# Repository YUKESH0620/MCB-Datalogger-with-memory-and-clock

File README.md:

# MCU Datalogger with Memory and Real-Time Clock

A compact, low-power data-logging board designed in KiCad (v9.0.4). The board is built around an ATmega328P-AU microcontroller, a DS1337S real-time clock (RTC) with a 32.768 kHz crystal, and two 24LC1025 I²C EEPROM devices for extended timestamped data storage. The design is a 2-layer custom PCB sized 87.63mm × 39.116mm and is powered by a coin-cell battery (BT1) for RTC backup. Data can be accessed via I²C or UART; the MCU is programmable by ICSP or a UART bootloader.

---

## Overview

This project is a lightweight, modular data logger intended for timestamped sensor data collection. It provides:

- Reliable timekeeping (DS1337S with coin-cell backup)
- Extended non-volatile storage (two 24LC1025 EEPROMs)
- Standard interfaces for integration (I²C, UART, GPIO, ICSP)
- A compact 2-layer PCB designed in KiCad 9.0.4

---

## Features

- Microcontroller: ATmega328P-AU (16 MHz)
- Real-time clock: DS1337S with 32.768 kHz crystal
- Non-volatile memory: 2 × 24LC1025 EEPROM (I²C)
- Connectivity: I²C header, UART (RX/TX) header, GPIO header, 6-pin ICSP
- Indicators: 2 status LEDs
- Power: Coin-cell Battery (BT1) for RTC backup
- Board: 2-layer PCB; 87.63 mm × 39.116 mm; 4 mounting holes
- KiCad version: 9.0.0

---

## Hardware Architecture

High-level blocks:

- MCU (ATmega328P-AU): central controller for data acquisition, timestamping, and storage
- RTC (DS1337S): battery-backed real-time clock (I²C)
- EEPROMs (2 × 24LC1025): extended I²C non-volatile storage
- Headers: I²C, UART, GPIO, and ICSP for programming and peripherals
- Power: Coin-cell for RTC backup; decoupling and power filtering on-board

Notable electrical details:

- MCU clock: 16 MHz crystal (Y2) with C2 = 22 pF and C3 = 22 pF
- RTC: DS1337S with 32.768 kHz crystal; pull-ups R1 = 10 kΩ, R2 = 10 kΩ; decoupling C1 = 0.1 µF
- EEPROMs: Two 24LC1025 on I²C with pull-ups R3 = 4.7 kΩ and R4 = 4.7 kΩ
- Status LEDs: D1 (R5 = 330 Ω), D2 (R7 = 330 Ω)
- Power decoupling: C4 = 0.1 µF

---

## Schematic

- Schematic Page 1 — Main MCU, RTC, EEPROM

- Schematic Page 2 — Connectors

Refer to the KiCad schematic files in the repo for full net names, pin labels, and design notes.

---

## PCB Layout
### 2 layer

### 4 layer

### 3D View

#### PCB summary

| Property | Value |
|---|---:|
| Layers | 2 |
| Dimensions | 87.63 mm × 39.116 mm |
| Mounting holes | 4 |
| Silkscreen | Labeled pins (I²C, UART, GPIO, ICSP) |
| Unrouted nets | 0 |
| KiCad version | 9.0 |

---

## Connectors / Pinout

- I²C header (4-pin): SDA, SCL, VCC, GND
- UART header (3-pin): RX, TX, GND (VCC optional)
- GPIO header: multiple MCU GPIO pins broken out (see schematic)
- ICSP (6-pin): MISO, MOSI, SCK, RESET, VCC, GND

---

## Bill of Materials (BOM)

| Ref | Qty | Part | Notes |
|---|---:|---|---|
| U1 | 1 | ATmega328P-AU | 28-pin TQFP |
| U2 | 1 | DS1337S | RTC (I²C) |
| U3, U4 | 2 | 24LC1025 | I²C EEPROM |
| Y2 | 1 | Crystal | 16 MHz (MCU) |
| Y1 | 1 | Crystal | 32.768 kHz (RTC) |
| BT1 | 1 | Battery | CR2032 or equivalent (observe polarity) |
| C1, C4 | 2 | 0.1 µF | Ceramic decoupling caps |
| C2, C3 | 2 | 22 pF | Crystal load caps |
| R1, R2 | 2 | 10 kΩ | RTC pull-ups |
| R3, R4 | 2 | 4.7 kΩ | EEPROM pull-ups |
| R5, R7 | 2 | 330 Ω | LED current-limiting |
| D1, D2 | 2 | LED | SMD or THT per footprint |
| J1 (I²C) | 1 | Header | 4-pin |
| J2 (UART) | 1 | Header | 3-pin |
| J3 (GPIO) | 1 | Header | n-pin |
| J4 (ICSP) | 1 | 6-pin ICSP | 2×3 2.54 mm |
| Mounting holes | 4 | M3 | Mechanical mounting |

Full, exportable BOM (CSV) and placement files are provided in the repo (see /bom and /fab folders if present).

---

## How to Use

Assembly:

- Solder SMD components first (MCU, RTC, EEPROMs, resistors, capacitors), then through-hole parts (headers, coin cell holder).
- Observe polarity for LEDs and coin cell.
- Place crystals and load capacitors as shown in schematic.

Power:

- Supply VCC according to the chosen components (3.3 V or 5 V depending on populated parts). Confirm the RTC and EEPROM voltage ranges before applying power.
- Coin cell provides RTC backup via the VBAT connection on the DS1337S. Ensure correct polarity and secure holder.

Basic operation:

- The MCU collects sensor data (I²C/GPIO), requests current time from the DS1337S, and writes time-stamped entries to the EEPROM(s).
- Retrieve logs via UART (connect a USB‑to‑TTL adapter: RX→TX, TX→RX, GND→GND) at the baud rate set by the firmware.
- Optionally access EEPROMs directly over I²C from a host microcontroller or logic analyzer.

I²C notes:

- On-board pull-ups are provided (R1/R2 for RTC, R3/R4 for EEPROM). If your external bus already includes pull-ups, verify combined pull-up resistance is within recommended limits.
- Addressing: consult the 24LC1025 datasheet for device addressing and block management if both EEPROMs use similar address pins.

---

## Programming the MCU

ICSP (recommended for initial programming and bootloader burn):

- Connect a 6-pin ISP programmer (USBasp, AVRISP, etc.) to the ICSP header: MISO, MOSI, SCK, RESET, VCC, GND.
- Example avrdude command (USBasp):

  avrdude -c usbasp -p m328p -U flash:w:firmware.hex

UART (if a bootloader is installed):

- Use a USB‑to‑TTL adapter to the UART header. Typical Arduino/Optiboot settings for 16 MHz apply if using Arduino core.
- To burn a bootloader via Arduino IDE, connect an ISP programmer and select the appropriate board/frequency, then Tools → Burn Bootloader.

Firmware recommendations:

- Implement time queries to DS1337S via I²C and write structured records to EEPROM with checksums.
- Implement wear-leveling or a ring-buffer log scheme to maximize EEPROM lifespan.
- Provide a simple UART command set for log extraction and configuration.

---

<!--## Testing & Validation

- Verify MCU oscillator and boot behavior after programming.
- Confirm RTC register reads/writes and timekeeping across coin-cell swaps.
- Use an I²C scanner to validate device addresses for RTC and EEPROMs.
- Test UART responses and data export functionality. -->

## Future Improvements

- Add optional power domain/regulator for external supplies with coin-cell backup for RTC.
- Add battery charging and low-battery detection circuitry.
- Add footprints for common sensors (temperature, humidity, pressure) on-board.
- Implement hardware write-protect for EEPROMs and optional encryption of stored logs.
- Provide a 3D-printable enclosure and mounting guides.

---

## Contributing

Contributions are welcome. Please:

- Open an issue to discuss non-trivial changes before submitting a PR.
- Submit focused pull requests with updated KiCad files, Gerbers, and BOM when hardware changes are included.
- Keep commit messages clear and include rationale for electrical or layout changes.

---

## Safety

- Coin cells are a choking hazard and can be dangerous if swallowed—keep away from children.
- Handle ESD-sensitive parts with appropriate precautions.
- Verify coin-cell polarity before installing.

---

## License

This project is provided under the MIT License. See LICENSE for details.

---

## Contacts

For questions or collaboration, open an issue or contact the repository owner (YUKESH0620) via GitHub.

---

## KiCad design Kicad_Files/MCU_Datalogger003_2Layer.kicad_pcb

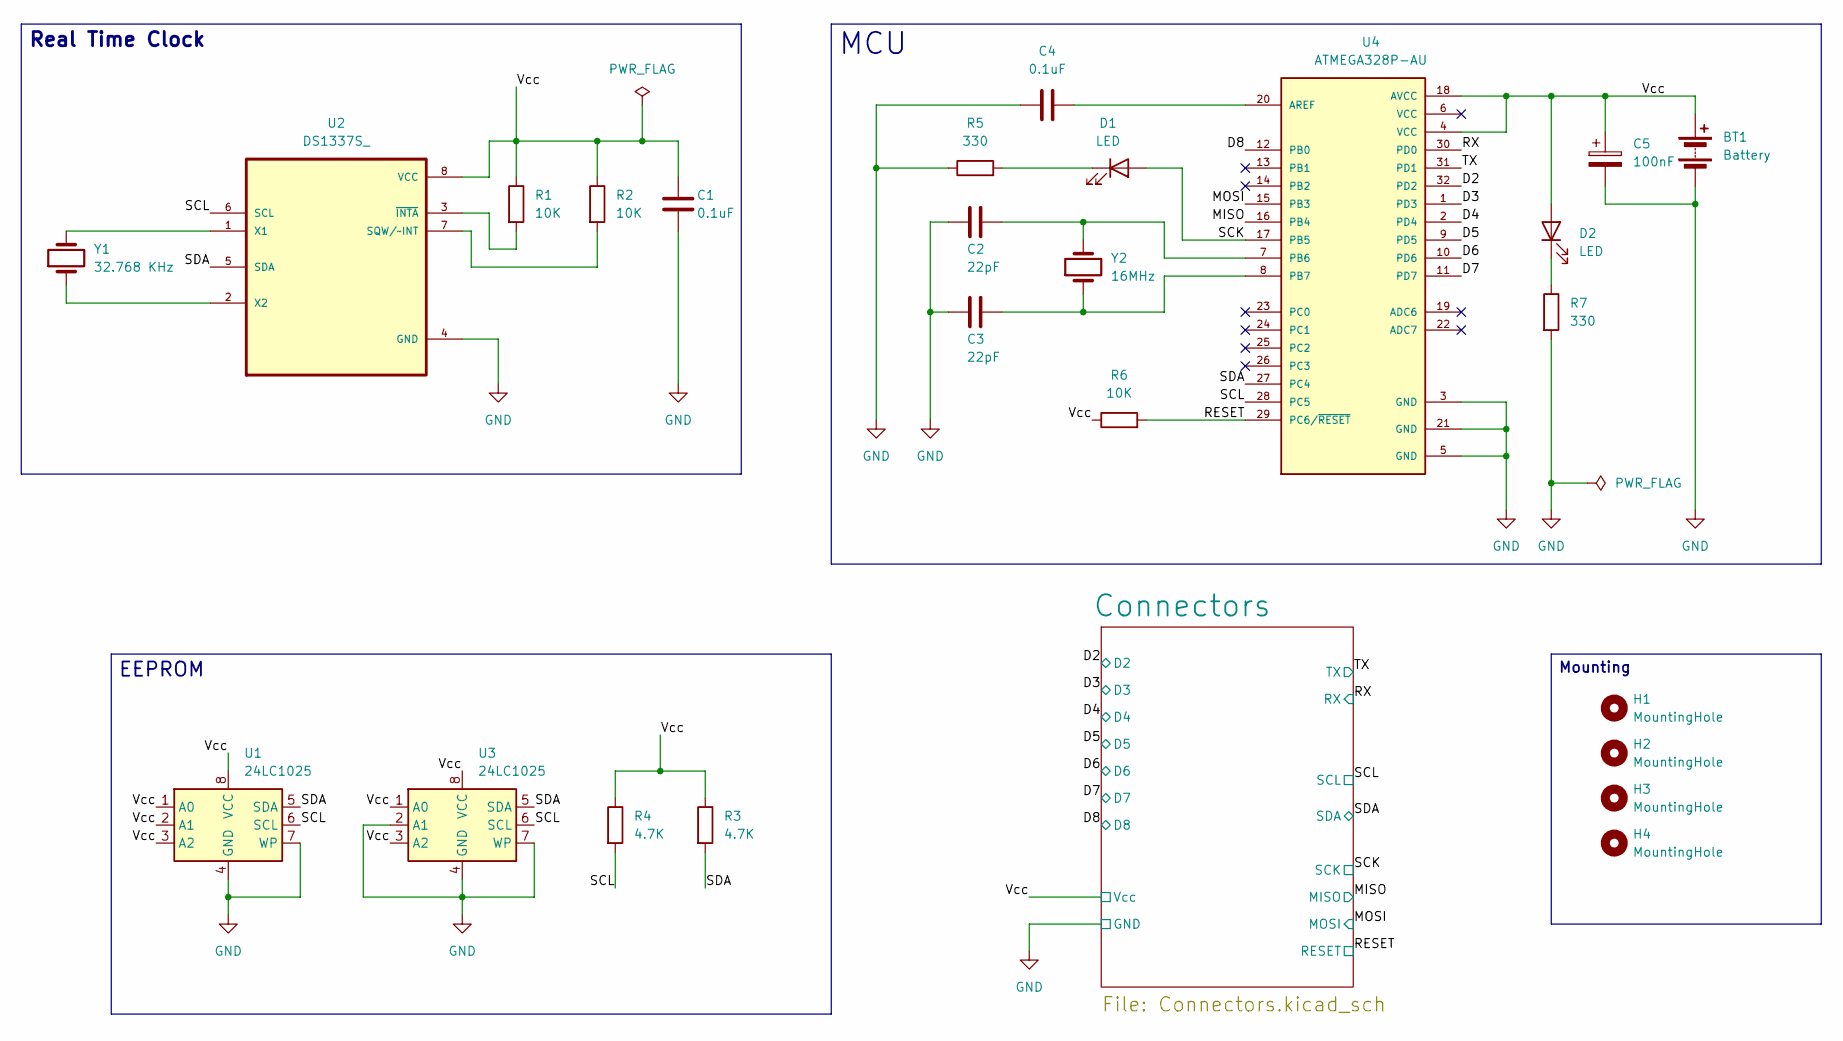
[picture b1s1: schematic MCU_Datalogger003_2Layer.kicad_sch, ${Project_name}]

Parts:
BT1: Battery; PinHeader_1x02_P2.54mm_Vertical
C1, C4: 0.1uF; C_0805_2012Metric
C2, C3: 22pF; C_0805_2012Metric
C5: 100nF; C_0805_2012Metric
D1, D2: LED; LED_0805_2012Metric
H1, H2, H3, H4: MountingHole; MountingHole_2.1mm
R1, R2, R6: 10K; R_0805_2012Metric
R3, R4: 4.7K; R_0805_2012Metric
R5, R7: 330; R_0805_2012Metric
U1, U3: 24LC1025; SOIC-8_5.3x5.3mm_P1.27mm
U2: DS1337S_; RT-CLOCK_SOIC127P600X175-8N
U4: ATMEGA328P-AU; ATMEGA328P-AUQFP80P900X900X120-32N; PARTREV 8271A
Y1: 32.768 KHz; Crystal_SMD_5032-2Pin_5.0x3.2mm_HandSoldering
Y2: 16MHz; Crystal_SMD_5032-2Pin_5.0x3.2mm_HandSoldering

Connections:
/D2: U4.32 (PD2); also elsewhere on the board
/D3: U4.1 (PD3); also elsewhere on the board
/D4: U4.2 (PD4); also elsewhere on the board
/D5: U4.9 (PD5); also elsewhere on the board
/D6: U4.10 (PD6); also elsewhere on the board
/D7: U4.11 (PD7); also elsewhere on the board
/D8: U4.12 (PB0); also elsewhere on the board
/MISO: U4.16 (PB4); also elsewhere on the board
/MOSI: U4.15 (PB3); also elsewhere on the board
/RESET: R6.2, U4.29 (PC6/~RESET); also elsewhere on the board
/RX: U4.30 (PD0); also elsewhere on the board
/SCK: D1.2 (A), U4.17 (PB5); also elsewhere on the board
/SCL: R4.2, U1.6 (SCL), U2.6 (SCL), U3.6 (SCL), U4.28 (PC5); also elsewhere on the board
/SDA: R3.2, U1.5 (SDA), U2.5 (SDA), U3.5 (SDA), U4.27 (PC4); also elsewhere on the board
/TX: U4.31 (PD1); also elsewhere on the board
/Vcc: BT1.1 (+), C1.1, C5.1, D2.2 (A), R1.1, R2.1, R3.1, R4.1, R6.1, U1.1 (A0), U1.2 (A1), U1.3 (A2), U1.8 (VCC), U2.8 (VCC), U3.1 (A0), U3.3 (A2), U3.8 (VCC), U4.4 (VCC), U4.18 (AVCC); also elsewhere on the board
GND: BT1.2 (-), C1.2, C2.2, C3.2, C4.1, C5.2, R5.1, R7.2, U1.4 (GND), U1.7 (WP), U2.4 (GND), U3.2 (A1), U3.4 (GND), U3.7 (WP), U4.3 (GND), U4.5 (GND), U4.21 (GND); also elsewhere on the board
unnamed: D1.1 (K), R5.2
unnamed: D2.1 (K), R7.1
unnamed: R2.2, U2.7 (SQW/~INT)
unnamed: U2.1 (X1), Y1.2
unnamed: U2.2 (X2), Y1.1
unnamed: R1.2, U2.3 (~INTA)
unnamed: C4.2, U4.20 (AREF)
unnamed: C2.1, U4.7 (PB6), Y2.2
unnamed: C3.1, U4.8 (PB7), Y2.1

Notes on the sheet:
EEPROM
Mounting
Real Time Clock
MCU

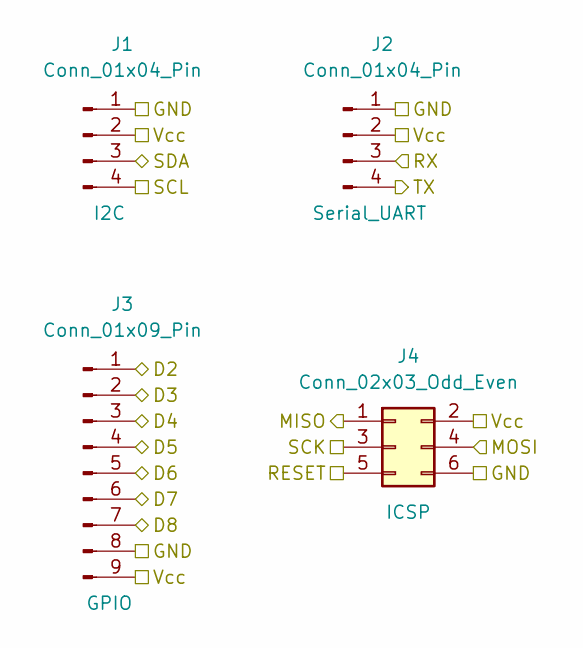
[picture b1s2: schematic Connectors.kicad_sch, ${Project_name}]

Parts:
J1, J2: Conn_01x04_Pin; PinHeader_1x04_P2.54mm_Vertical
J3: Conn_01x09_Pin; PinHeader_1x09_P2.54mm_Vertical
J4: Conn_02x03_Odd_Even; PinHeader_2x03_P2.54mm_Vertical

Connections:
/D2: J3.1; also elsewhere on the board
/D3: J3.2; also elsewhere on the board
/D4: J3.3; also elsewhere on the board
/D5: J3.4; also elsewhere on the board
/D6: J3.5; also elsewhere on the board
/D7: J3.6; also elsewhere on the board
/D8: J3.7; also elsewhere on the board
/MISO: J4.1; also elsewhere on the board
/MOSI: J4.4; also elsewhere on the board
/RESET: J4.5; also elsewhere on the board
/RX: J2.3; also elsewhere on the board
/SCK: J4.3; also elsewhere on the board
/SCL: J1.4; also elsewhere on the board
/SDA: J1.3; also elsewhere on the board
/TX: J2.4; also elsewhere on the board
/Vcc: J1.2, J2.2, J3.9, J4.2; also elsewhere on the board
GND: J1.1, J2.1, J3.8, J4.6; also elsewhere on the board

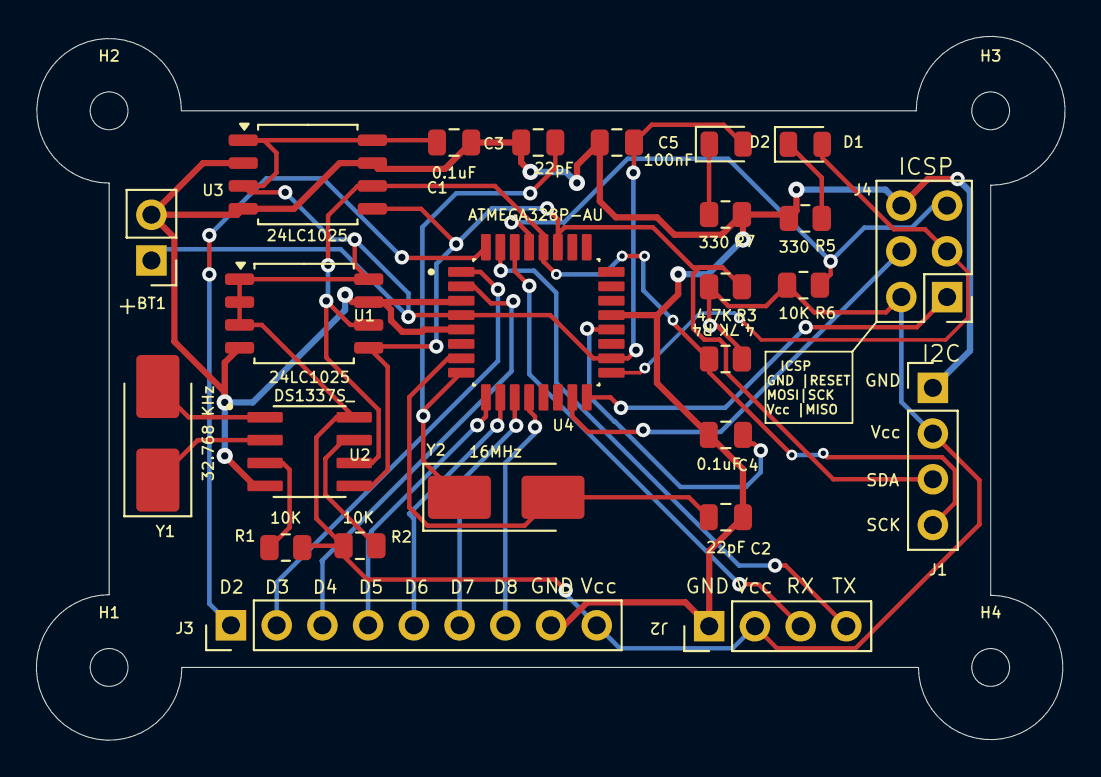
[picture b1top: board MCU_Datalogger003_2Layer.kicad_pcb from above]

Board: 2 copper layers, 57.1 x 39.1 mm, 29 parts (0 on the bottom side), 26 nets.

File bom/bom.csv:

Ref,Quantity,Part,Value/Notes,Footprint,Manufacturer,MPN,
U1,1,ATmega328P-AU,Microcontroller,TQFP-32,Microchip,ATMEGA328P-AU,
U2,1,DS1337S,RTC (I2C),SOIC-8,Maxim,DS1337S,
U3,1,24LC1025,I2C EEPROM,SOIC-8,Microchip,24LC1025,
U4,1,24LC1025,I2C EEPROM,SOIC-8,Microchip,24LC1025,
Y2,1,Crystal,16 MHz (MCU),SMD,Various,
Y1,1,Crystal,32.768 kHz (RTC),SMD,Various,
BT1,1,Coin cell holder,CR2032 holder,Through-hole,Various,
C1,1,Capacitor,0.1 uF,0603,Ceramic,
C4,1,Capacitor,0.1 uF,0603,Ceramic,
C2,1,Capacitor,22 pF,0603,Ceramic,
C3,1,Capacitor,22 pF,0603,Ceramic,
R1,1,Resistor,10 kOhm (RTC pull-up),0603,Various,
R2,1,Resistor,10 kOhm (RTC pull-up),0603,Various,
R3,1,Resistor,4.7 kOhm (EEPROM pull-up),0603,Various,
R4,1,Resistor,4.7 kOhm (EEPROM pull-up),0603,Various,
R5,1,Resistor,330 Ohm (LED),0603,Various,
R7,1,Resistor,330 Ohm (LED),0603,Various,
D1,1,LED,Status LED,SMD-0805,Various,
D2,1,LED,Status LED,SMD-0805,Various,
J1,1,Header,I2C 4-pin,Header-1x4,Various,
J2,1,Header,UART 3-pin,Header-1x3,Various,
J3,1,Header,GPIO header,Header-1xN,Various,
J4,1,Header,ICSP 6-pin (2x3),2x3 2.54mm,Various,
MH1,4,Mounting hole,M3 mounting hole,Mechanical,Various,

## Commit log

2025-12-09 Add BOM CSV
2025-12-09 Create Gerber Files
2025-12-09 Rename Gerber Files to Gerber Files_2layer
